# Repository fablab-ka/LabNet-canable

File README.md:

#LabNet-canable

a fork of canable  
Easy access the LabNet from any PC and integrate Raspberry PIs and Beaglebones in the Infrastructure.

### Original Design 

from Ethan Zonca.  
http://protofusion.org/wordpress/2015/05/the-canable-a-small-usb-to-can-adapter/  
http://hg.protofusion.org/canable  

### modified Firmware of CANtact
https://github.com/normaldotcom/CANtact

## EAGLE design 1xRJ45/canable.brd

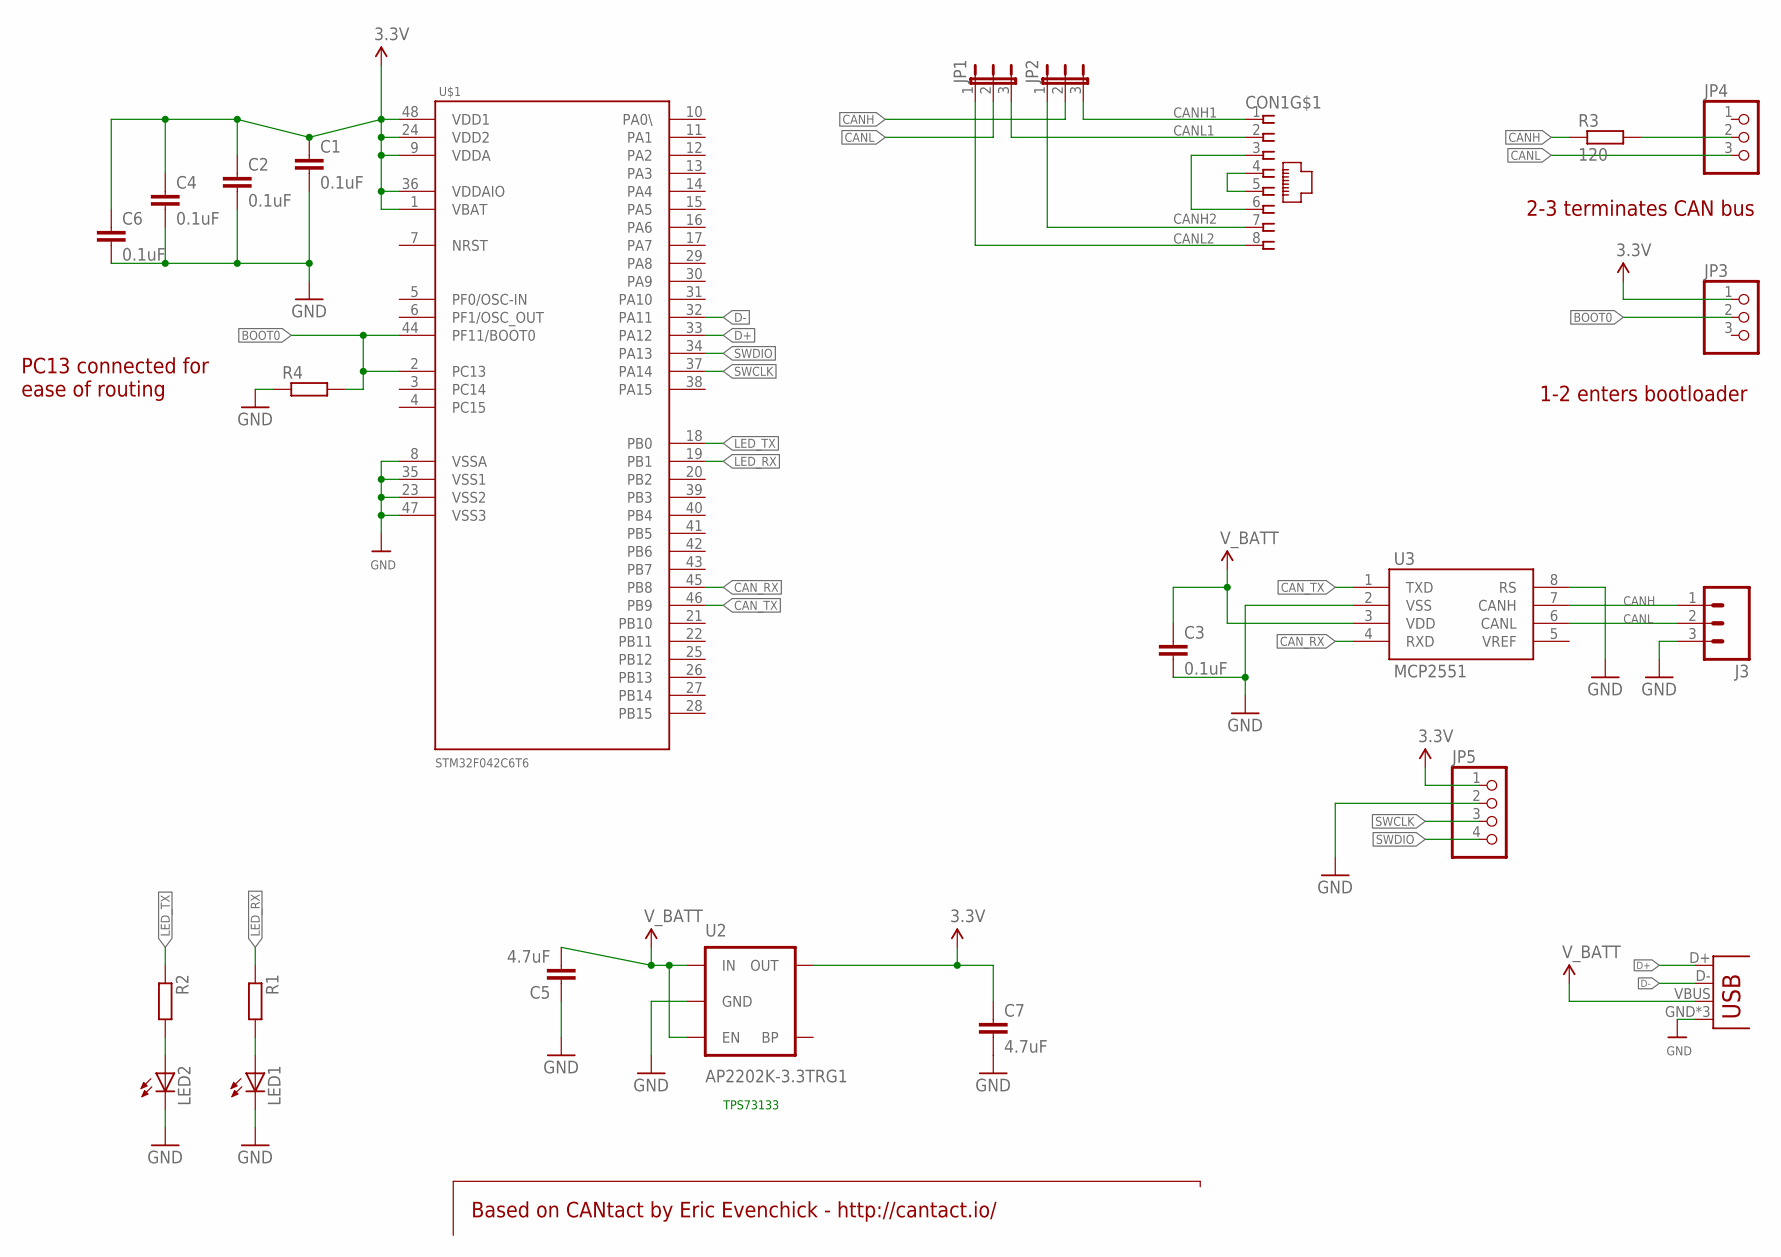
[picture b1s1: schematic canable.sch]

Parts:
C1, C2, C3, C4, C6: 0.1uF; C0805
C5, C7: 4.7uF; C0805
CON1: MEBP_8-8G; MEBP
J2: USB-MICROB
J3: M03SCREW_LOCK; SCREWTERMINAL-3.5MM-3_LOCK.007S
JP1, JP2: JP2E; JP2
JP3, JP4: PINHD-1X3; 1X03
JP5: PINHD-1X4; 1X04
LED1, LED2: LEDCHIPLED_1206; CHIPLED_1206
R1, R2, R4: R-EU_R0805; R0805
R3: 120; R0805
U2: AP2202K-3.3TRG1; SOT23-5
U3: MCP2551; SO08
U$1: STM32F042C6T6; LQFP48

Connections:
3.3V: C1.1, C2.1, C4.1, C6.1, C7.1, JP3.1, JP5.1, U2.5 (OUT), U$1.1 (VBAT), U$1.9 (VDDA), U$1.24 (VDD2), U$1.36 (VDDAIO), U$1.48 (VDD1)
BOOT0: JP3.2, R4.2, U$1.2 (PC13), U$1.44 (PF11/BOOT0)
CANH: J3.1, JP2.2, R3.1, U3.7 (CANH)
CANH1: CON1.1, JP2.3
CANH2: CON1.7, JP2.1
CANL: J3.2, JP1.2, JP4.3, U3.6 (CANL)
CANL1: CON1.2, JP1.3
CANL2: CON1.8, JP1.1
CAN_RX: U3.4 (RXD), U$1.45 (PB8)
CAN_TX: U3.1 (TXD), U$1.46 (PB9)
D+: J2.D+, U$1.33 (PA12)
D-: J2.D-, U$1.32 (PA11)
FGND: CON1.T1 (FGND), CON1.T2 (FGND)
GND: C1.2, C2.2, C3.2, C4.2, C5.1, C6.2, C7.2, J2.GND, J2.MT1 (GND), J2.MT2 (GND), J3.3, JP5.2, LED1.C, LED2.C, R4.1, U2.2 (GND), U3.2 (VSS), U3.8 (RS), U$1.8 (VSSA), U$1.23 (VSS2), U$1.35 (VSS1), U$1.47 (VSS3)
LED_RX: R1.1, U$1.19 (PB1)
LED_TX: R2.1, U$1.18 (PB0)
unnamed: CON1.3, CON1.6
unnamed: LED2.A, R2.2
unnamed: JP4.2, R3.2
unnamed: CON1.4, CON1.5
unnamed: LED1.A, R1.2
SWCLK: JP5.3, U$1.37 (PA14)
SWDIO: JP5.4, U$1.34 (PA13)
V_BATT: C3.1, C5.2, J2.VBUS, U2.1 (IN), U2.3 (EN), U3.3 (VDD)

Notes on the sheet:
Based on CANtact by Eric Evenchick - http://cantact.io/
PC13 connected for ease of routing
2-3 terminates CAN bus
1-2 enters bootloader
TPS73133

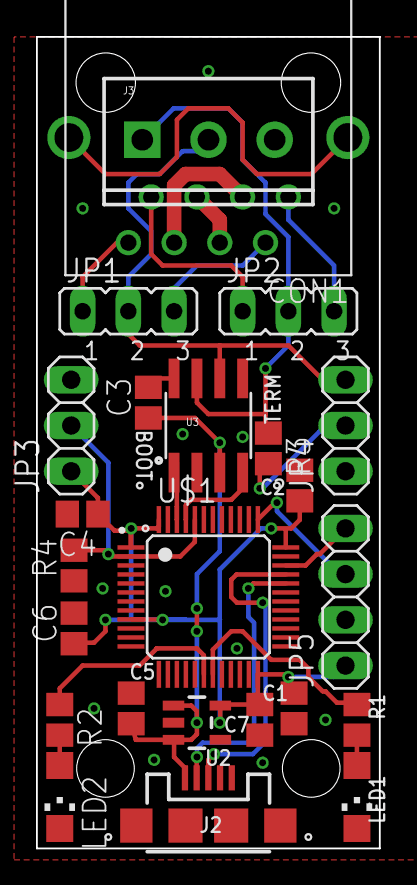
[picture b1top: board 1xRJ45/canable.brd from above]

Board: 2 copper layers, 19.1 x 45.1 mm, 25 parts (1 on the bottom side), 24 nets.

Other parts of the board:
U$2: CANABLE-LOGO

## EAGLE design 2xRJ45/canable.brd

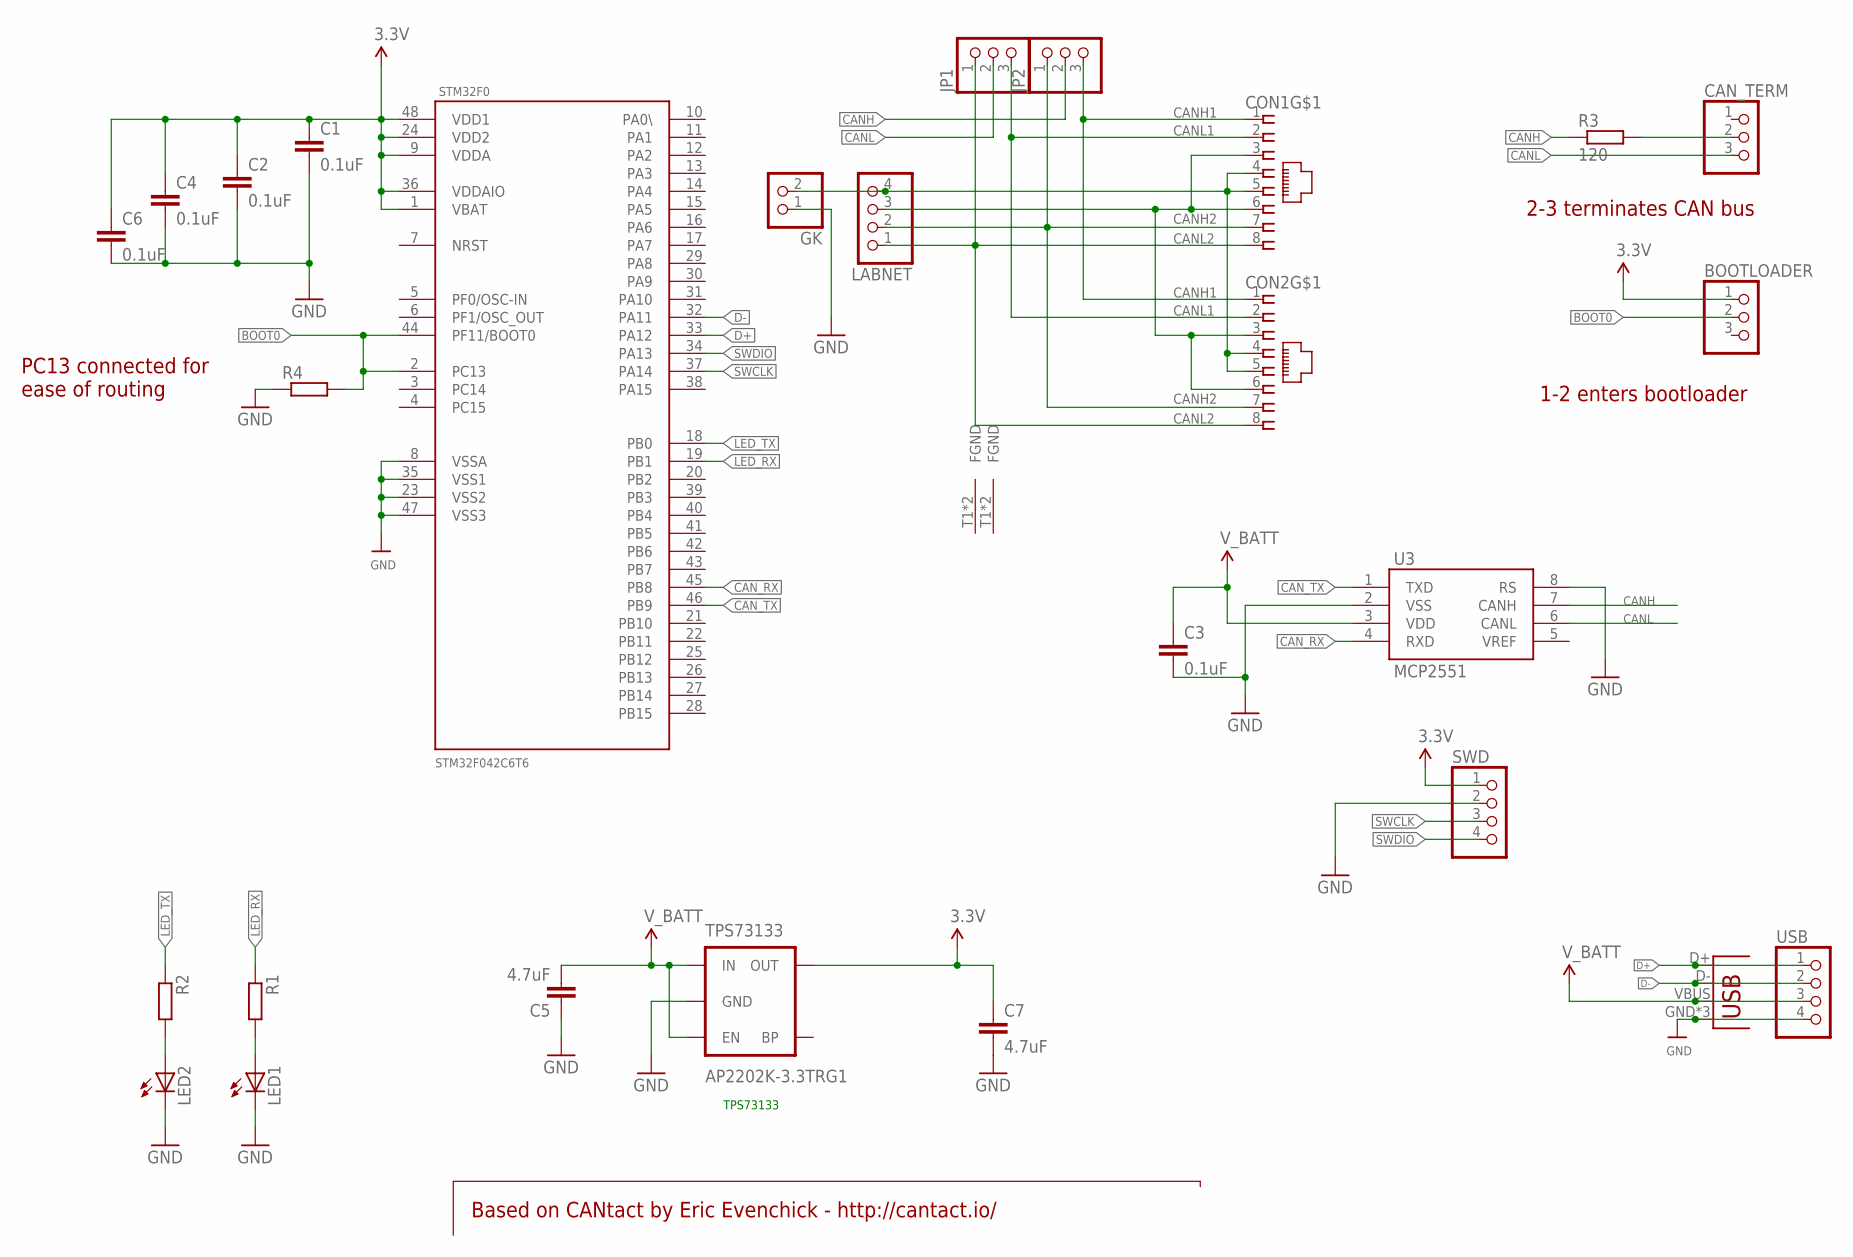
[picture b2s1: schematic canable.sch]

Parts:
BOOTLOADER: PINHD-1X3; 1X03
C1, C2, C3, C4, C6: 0.1uF; C0805
C5, C7: 4.7uF; C0805
CAN_TERM: PINHD-1X3; 1X03
CON1, CON2: MEBP_8-8G; MEBP
GK: PINHD-1X2; 1X02
J2: USB-MICROB
JP1, JP2: PINHD-1X3; 1X03
LABNET: PINHD-1X4; 1X04
LED1, LED2: LEDCHIPLED_1206; CHIPLED_1206
R1, R2, R4: R-EU_R0805; R0805
R3: 120; R0805
STM32F0: STM32F042C6T6; LQFP48
SWD: PINHD-1X4; 1X04
TPS73133: AP2202K-3.3TRG1; SOT23-5
U3: MCP2551; SO08
USB: PINHD-1X4; 1X04

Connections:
3.3V: BOOTLOADER.1, C1.1, C2.1, C4.1, C6.1, C7.1, STM32F0.1 (VBAT), STM32F0.9 (VDDA), STM32F0.24 (VDD2), STM32F0.36 (VDDAIO), STM32F0.48 (VDD1), SWD.1, TPS73133.5 (OUT)
BOOT0: BOOTLOADER.2, R4.2, STM32F0.2 (PC13), STM32F0.44 (PF11/BOOT0)
CANH: JP2.2, R3.1, U3.7 (CANH)
CANH1: CON1.1, CON2.1, JP2.3
CANH2: CON1.7, CON2.7, JP2.1, LABNET.2
CANL: CAN_TERM.3, JP1.2, U3.6 (CANL)
CANL1: CON1.2, CON2.2, JP1.3
CANL2: CON1.8, CON2.8, JP1.1, LABNET.1
CAN_RX: STM32F0.45 (PB8), U3.4 (RXD)
CAN_TX: STM32F0.46 (PB9), U3.1 (TXD)
D+: J2.D+, STM32F0.33 (PA12), USB.1
D-: J2.D-, STM32F0.32 (PA11), USB.2
FGND: CON1.T1 (FGND), CON1.T2 (FGND), CON2.T1 (FGND), CON2.T2 (FGND)
GND: C1.2, C2.2, C3.2, C4.2, C5.1, C6.2, C7.2, GK.1, J2.GND, J2.MT1 (GND), J2.MT2 (GND), LED1.C, LED2.C, R4.1, STM32F0.8 (VSSA), STM32F0.23 (VSS2), STM32F0.35 (VSS1), STM32F0.47 (VSS3), SWD.2, TPS73133.2 (GND), U3.2 (VSS), U3.8 (RS), USB.4
LED_RX: R1.1, STM32F0.19 (PB1)
LED_TX: R2.1, STM32F0.18 (PB0)
unnamed: LED2.A, R2.2
unnamed: CAN_TERM.2, R3.2
unnamed: CON1.3, CON1.6, CON2.3, CON2.6, LABNET.3
unnamed: CON1.4, CON1.5, CON2.4, CON2.5, GK.2, LABNET.4
unnamed: LED1.A, R1.2
SWCLK: STM32F0.37 (PA14), SWD.3
SWDIO: STM32F0.34 (PA13), SWD.4
V_BATT: C3.1, C5.2, J2.VBUS, TPS73133.1 (IN), TPS73133.3 (EN), U3.3 (VDD), USB.3

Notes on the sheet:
Based on CANtact by Eric Evenchick - http://cantact.io/
PC13 connected for ease of routing
2-3 terminates CAN bus
1-2 enters bootloader
TPS73133

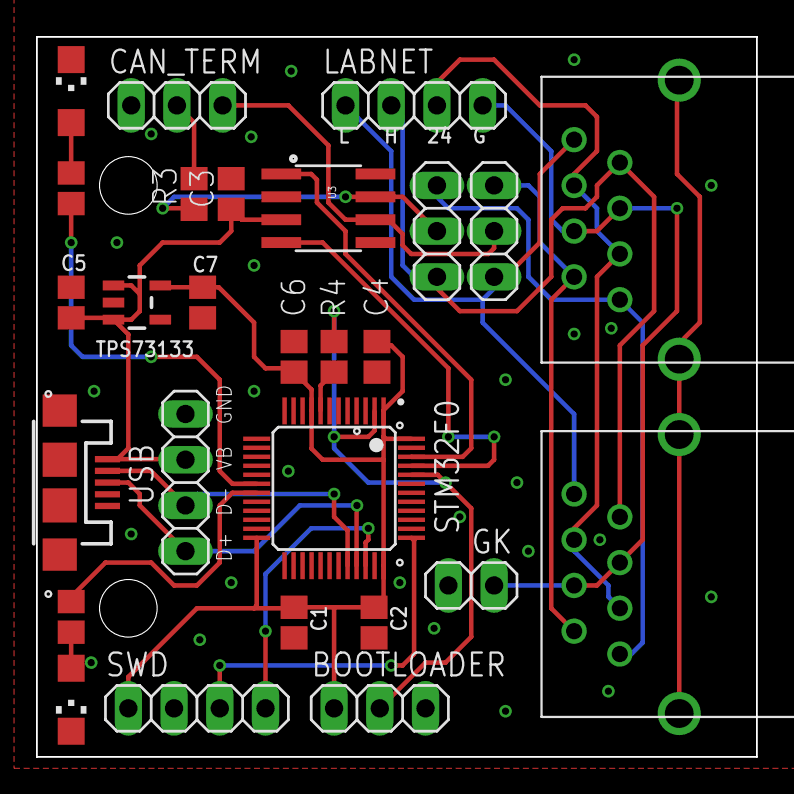
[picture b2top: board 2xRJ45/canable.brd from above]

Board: 2 copper layers, 40.0 x 40.0 mm, 27 parts (0 on the bottom side), 24 nets.

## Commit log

2015-07-03 init
2015-07-03 bom changed and screw holes added
2015-07-03 readme and image

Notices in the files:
parts and their libraries:
SparkFun-Connectors: Licensing: Creative Commons ShareAlike 4.0 International - https://creativecommons.org/licenses/by-sa/4.0
